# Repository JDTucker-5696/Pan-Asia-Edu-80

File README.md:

# Pan-Asia-Edu-80
Information about the Pan-Asia Edu-80 Z80 training system.

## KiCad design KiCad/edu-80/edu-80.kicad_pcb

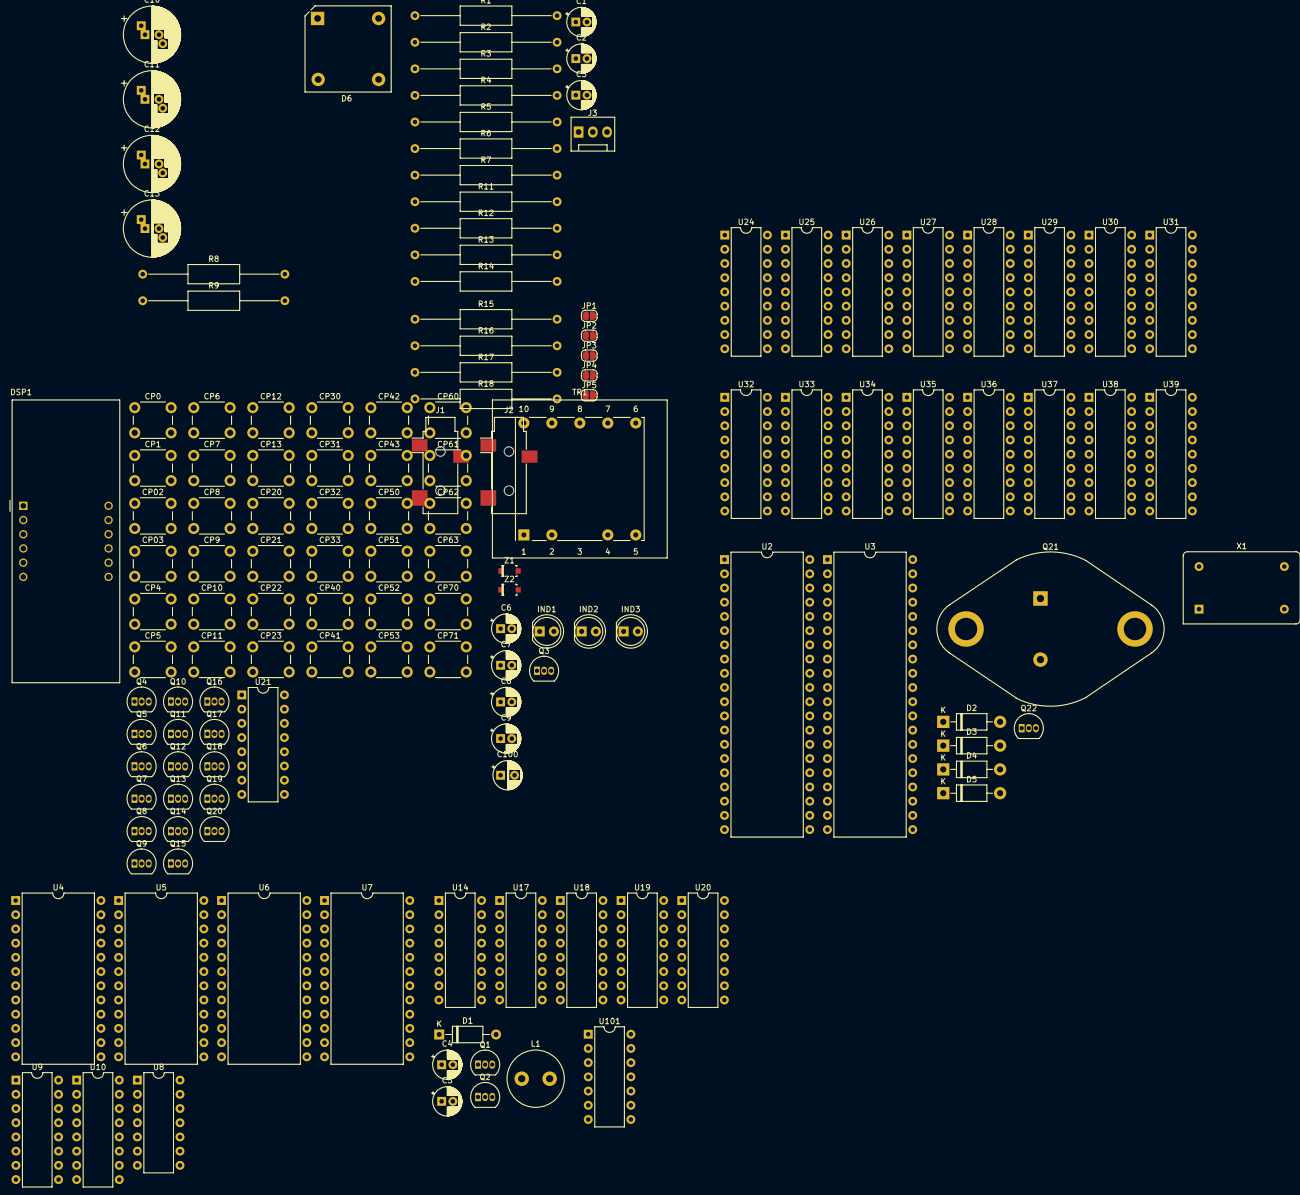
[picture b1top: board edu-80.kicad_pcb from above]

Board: 2 copper layers, 144 parts (0 on the bottom side), 110 nets, no tracks yet.

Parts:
C1: 20p; CP_Radial_D5.0mm_P2.00mm
C2: 10p; CP_Radial_D5.0mm_P2.00mm
C3: 250p; CP_Radial_D5.0mm_P2.00mm
C4, C5: 1uF; CP_Radial_D5.0mm_P2.00mm
C6, C7, C8, C9: 0.01uF; CP_Radial_D5.0mm_P2.00mm
C10, C13: 1000 uF (16v); CP_Radial_D10.0mm_P2.50mm_P5.00mm
C11: 100 uF (16v); CP_Radial_D10.0mm_P2.50mm_P5.00mm
C12: 2200 uF (16v); CP_Radial_D10.0mm_P2.50mm_P5.00mm
C100: 0.01uF; CP_Radial_D5.0mm_P2.50mm
CP0: 0; SW_PUSH_6mm
CP1: 1; SW_PUSH_6mm
CP02: 2; SW_PUSH_6mm
CP03: 3; SW_PUSH_6mm
CP4: RS; SW_PUSH_6mm
CP5: CK; SW_PUSH_6mm
CP6: K1; SW_PUSH_6mm
CP7: K2; SW_PUSH_6mm
CP8: K3; SW_PUSH_6mm
CP9: K4; SW_PUSH_6mm
CP10: 4; SW_PUSH_6mm
CP11: 5; SW_PUSH_6mm
CP12: 6; SW_PUSH_6mm
CP13: 7; SW_PUSH_6mm
CP20: 8; SW_PUSH_6mm
CP21: 9; SW_PUSH_6mm
CP22: A; SW_PUSH_6mm
CP23: B; SW_PUSH_6mm
CP30: C; SW_PUSH_6mm
CP31: D; SW_PUSH_6mm
CP32: E; SW_PUSH_6mm
CP33: F; SW_PUSH_6mm
CP40: GO; SW_PUSH_6mm
CP41: BR; SW_PUSH_6mm
CP42: PC; SW_PUSH_6mm
CP43: RG; SW_PUSH_6mm
CP50: MV; SW_PUSH_6mm
CP51: BN; SW_PUSH_6mm
CP52: TD; SW_PUSH_6mm
CP53: TL; SW_PUSH_6mm
CP60: RL; SW_PUSH_6mm
CP61: WI; SW_PUSH_6mm
CP62: AD; SW_PUSH_6mm
CP63: BI; SW_PUSH_6mm
CP70: +; SW_PUSH_6mm
CP71: -; SW_PUSH_6mm
D1: 1N914; D_A-405_P10.16mm_Horizontal
D2, D3, D4, D5: 1N4005; D_DO-41_SOD81_P10.16mm_Horizontal
D6: D_Bridge_+-AA; Diode_Bridge_15.1x15.1x6.3mm_P10.9mm
DSP1: Edu-80_Display; CA56-12EWA
IND1: HALT; LED_D5.0mm
IND2: WAIT; LED_D5.0mm
IND3: M1; LED_D5.0mm
J1: Audio Out; Jack_3.5mm_CUI_SJ-3523-SMT_Horizontal
J2: Audio In; Jack_3.5mm_CUI_SJ-3523-SMT_Horizontal
J3: Conn_01x03; FanPinHeader_1x03_P2.54mm_Vertical
JP1, JP2, JP3, JP4, JP5: SolderJumper_2_Open; SolderJumper-2_P1.3mm_Open_RoundedPad1.0x1.5mm
L1: 2MHz; L_Radial_D10.0mm_P5.00mm_Fastron_07M
Q1, Q2, Q3: ED1402; TO-92_Inline
Q4, Q5, Q6, Q7, Q8, Q9, Q10, Q11, Q12, Q13, Q14, Q15, Q16, Q17, Q18, Q19, Q20: ED1602; TO-92_Inline
Q21: 2N3055; TO-3
Q22: 2N3906; TO-92_Inline
R1, R15: 330; R_Axial_DIN0309_L9.0mm_D3.2mm_P25.40mm_Horizontal
R2, R11, R12, R13, R14: 4.7K; R_Axial_DIN0309_L9.0mm_D3.2mm_P25.40mm_Horizontal
R3: 1M; R_Axial_DIN0309_L9.0mm_D3.2mm_P25.40mm_Horizontal
R4, R5, R16, R17: 10K; R_Axial_DIN0309_L9.0mm_D3.2mm_P25.40mm_Horizontal
R6: 30K; R_Axial_DIN0309_L9.0mm_D3.2mm_P25.40mm_Horizontal
R7: 100K; R_Axial_DIN0309_L9.0mm_D3.2mm_P25.40mm_Horizontal
R8, R9: 470; R_Axial_DIN0309_L9.0mm_D3.2mm_P25.40mm_Horizontal
R18: 1K; R_Axial_DIN0309_L9.0mm_D3.2mm_P25.40mm_Horizontal
TR1: TRANSF7; Transformer_Breve_TEZ-28x33
U2: Z84C20; DIP-40_W15.24mm
U3: Z8430_CTC; DIP-40_W15.24mm
U4, U7: EPROM-2708; DIP-24_W15.24mm
U5: 2708_(2716); DIP-24_W15.24mm
U6: 6116_RAM; DIP-24_W15.24mm
U8: SN7432; DIP-14_W7.62mm
U9, U10, U21: 7442; DIP-16_W7.62mm
U14: PAL-002; DIP-16_W7.62mm
U17: PAL-001; DIP-16_W7.62mm
U18: CD4051; DIP-16_W7.62mm
U19, U20: CD4099; DIP-16_W7.62mm
U24, U25, U26, U27, U28, U29, U30, U31, U32, U33, U34, U35, U36, U37, U38, U39: 2111A; DIP-18_W7.62mm
U101: 7408; DIP-14_W7.62mm
X1: 20MHz Ocillator; Oscillator_DIP-14
Z1: 12.6v; SOD-123
Z2: 5.6v; SOD-123

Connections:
+5V: C11.1, C100.1, D1.1 (K), Q4.1 (E), Q5.1 (E), Q6.1 (E), Q7.1 (E), Q8.1 (E), Q9.1 (E), Q10.1 (E), Q11.1 (E), R1.1, R2.1, R4.1, R5.1, R7.2, R11.1, R12.1, R13.1, R14.1, R18.1, U2.26 (VCC), U3.24 (VCC), U4.18 (~PGM), U4.24 (VCC), U5.18 (~PGM_(~CE)), U5.24 (VCC), U6.24 (VCC), U7.18 (~PGM), U7.24 (VCC), U9.16 (VCC), U10.16 (VCC), U14.16 (VCC), U17.16 (VCC), U18.16 (VCC), U19.16 (VDD), U20.16 (VDD), U21.16 (VCC), U24.18 (VCC), U25.18 (VCC), U26.18 (VCC), U27.18 (VCC), U28.18 (VCC), U29.18 (VCC), U30.18 (VCC), U31.18 (VCC), U32.18 (VCC), U33.18 (VCC), U34.18 (VCC), U35.18 (VCC), U36.18 (VCC), U37.18 (VCC), U38.18 (VCC), U39.18 (VCC), U101.14 (VCC), X1.14 (Vcc)
+12V: JP1.1 (A), JP1.2 (B), JP4.1 (A), JP4.2 (B), Q21.2 (E), U4.19 (+12), U7.19 (+12)
-5V: JP2.1 (A), JP2.2 (B), JP3.1 (A), JP5.1 (A), JP5.2 (B), Q22.1 (E), U4.21 (-5V), U7.21 (-5V)
-ATI: C100.2, U18.1 (Y4)
A0: U2.6 (B/~A), U3.18 (CS0), U4.8 (A0), U5.8 (A0), U6.8 (A0), U7.8 (A0), U18.11 (S1), U19.5 (A0), U20.5 (A0), U24.17 (A4), U25.17 (A4), U26.17 (A4), U27.17 (A4), U28.17 (A4), U29.17 (A4), U30.17 (A4), U31.17 (A4), U32.17 (A4), U33.17 (A4), U34.17 (A4), U35.17 (A4), U36.17 (A4), U37.17 (A4), U38.17 (A4), U39.17 (A4)
A1: U2.5 (C/~D), U3.19 (CS1), U4.7 (A1), U5.7 (A1), U6.7 (A1), U7.7 (A1), U18.10 (S2), U19.6 (A1), U20.6 (A1), U24.7 (A7), U25.7 (A7), U26.7 (A7), U27.7 (A7), U28.7 (A7), U29.7 (A7), U30.7 (A7), U31.7 (A7), U32.7 (A7), U33.7 (A7), U34.7 (A7), U35.7 (A7), U36.7 (A7), U37.7 (A7), U38.7 (A7), U39.7 (A7)
A2: U4.6 (A2), U5.6 (A2), U6.6 (A2), U7.6 (A2), U18.9 (S3), U19.7 (A2), U20.7 (A2), U24.6 (A6), U25.6 (A6), U26.6 (A6), U27.6 (A6), U28.6 (A6), U29.6 (A6), U30.6 (A6), U31.6 (A6), U32.6 (A6), U33.6 (A6), U34.6 (A6), U35.6 (A6), U36.6 (A6), U37.6 (A6), U38.6 (A6), U39.6 (A6)
A3: U4.5 (A3), U5.5 (A3), U6.5 (A3), U7.5 (A3), U14.11 (D), U24.5 (A5), U25.5 (A5), U26.5 (A5), U27.5 (A5), U28.5 (A5), U29.5 (A5), U30.5 (A5), U31.5 (A5), U32.5 (A5), U33.5 (A5), U34.5 (A5), U35.5 (A5), U36.5 (A5), U37.5 (A5), U38.5 (A5), U39.5 (A5)
A4: U4.4 (A4), U5.4 (A4), U6.4 (A4), U7.4 (A4), U14.12 (C), U24.4 (A0), U25.4 (A0), U26.4 (A0), U27.4 (A0), U28.4 (A0), U29.4 (A0), U30.4 (A0), U31.4 (A0), U32.4 (A0), U33.4 (A0), U34.4 (A0), U35.4 (A0), U36.4 (A0), U37.4 (A0), U38.4 (A0), U39.4 (A0)
A5: U4.3 (A5), U5.3 (A5), U6.3 (A5), U7.3 (A5), U14.13 (B), U24.3 (A1), U25.3 (A1), U26.3 (A1), U27.3 (A1), U28.3 (A1), U29.3 (A1), U30.3 (A1), U31.3 (A1), U32.3 (A1), U33.3 (A1), U34.3 (A1), U35.3 (A1), U36.3 (A1), U37.3 (A1), U38.3 (A1), U39.3 (A1)
A6: U4.2 (A6), U5.2 (A6), U6.2 (A6), U7.2 (A6), U14.10 (A), U24.2 (A2), U25.2 (A2), U26.2 (A2), U27.2 (A2), U28.2 (A2), U29.2 (A2), U30.2 (A2), U31.2 (A2), U32.2 (A2), U33.2 (A2), U34.2 (A2), U35.2 (A2), U36.2 (A2), U37.2 (A2), U38.2 (A2), U39.2 (A2)
A7: U4.1 (A7), U5.1 (A7), U6.1 (A7), U7.1 (A7), U17.10 (A), U24.1 (A3), U25.1 (A3), U26.1 (A3), U27.1 (A3), U28.1 (A3), U29.1 (A3), U30.1 (A3), U31.1 (A3), U32.1 (A3), U33.1 (A3), U34.1 (A3), U35.1 (A3), U36.1 (A3), U37.1 (A3), U38.1 (A3), U39.1 (A3)
A8: U4.23 (A8), U5.23 (A8), U6.23 (A8), U7.23 (A8), U10.15 (A0)
A9: U4.22 (A9), U5.22 (A9), U6.22 (A9), U7.22 (A9), U10.14 (A1)
A10: U5.19 (+12_(A10)), U6.19 (A10), U9.15 (A0), U10.13 (A2)
CKCTL: R4.2, U20.1 (Q7)
CKKEY: CP5.1 (X1), R5.2, R6.2
CLK: Q1.3 (C), R1.2, U2.25 (CLK), U3.15 (CLK)
CM1: U9.5 (~Q4), U24.15 (~CE2), U25.15 (~CE2), U26.15 (~CE2), U27.15 (~CE2), U28.15 (~CE2), U29.15 (~CE2), U30.15 (~CE2), U31.15 (~CE2)
CM2: U9.6 (~Q5), U32.15 (~CE2), U33.15 (~CE2), U34.15 (~CE2), U35.15 (~CE2), U36.15 (~CE2), U37.15 (~CE2), U38.15 (~CE2), U39.15 (~CE2)
D0: U2.19 (D0), U3.25 (D0), U4.9 (D0), U5.9 (D0), U6.9 (D0), U7.9 (D0), U19.3 (Din), U20.3 (Din), U24.13 (D3), U26.13 (D3), U28.13 (D3), U30.13 (D3), U32.13 (D3), U34.13 (D3), U36.13 (D3), U38.13 (D3)
D1: U2.20 (D1), U4.10 (D1), U5.10 (D1), U6.10 (D1), U7.10 (D1), U24.12 (D2), U26.12 (D2), U28.12 (D2), U30.12 (D2), U32.12 (D2), U34.12 (D2), U36.12 (D2), U38.12 (D2)
D2: U2.1 (D2), U3.27 (D2), U4.11 (D2), U5.11 (D2), U6.11 (D2), U7.11 (D2), U24.11 (D1), U26.11 (D1), U28.11 (D1), U30.11 (D1), U32.11 (D1), U34.11 (D1), U36.11 (D1), U38.11 (D1)
D3: U2.40 (D3), U3.28 (D3), U4.13 (D3), U5.13 (D3), U6.13 (D3), U7.13 (D3), U24.14 (D4), U26.14 (D4), U28.14 (D4), U30.14 (D4), U32.14 (D4), U34.14 (D4), U36.14 (D4), U38.14 (D4)
D4: U2.39 (D4), U3.1 (D4), U4.14 (D4), U5.14 (D4), U6.14 (D4), U7.14 (D4), U25.14 (D4), U27.14 (D4), U29.14 (D4), U31.14 (D4), U33.14 (D4), U35.14 (D4), U37.14 (D4), U39.14 (D4)
D5: U2.38 (D5), U3.2 (D5), U4.15 (D5), U5.15 (D5), U6.15 (D5), U7.15 (D5), U25.13 (D3), U27.13 (D3), U29.13 (D3), U31.13 (D3), U33.13 (D3), U35.13 (D3), U37.13 (D3), U39.13 (D3)
D6: U2.3 (D6), U3.3 (D6), U4.16 (D6), U5.16 (D6), U6.16 (D6), U7.16 (D6), U25.12 (D2), U27.12 (D2), U29.12 (D2), U31.12 (D2), U33.12 (D2), U35.12 (D2), U37.12 (D2), U39.12 (D2)
D7: U2.2 (D7), U3.4 (D7), U4.17 (D7), U5.17 (D7), U6.17 (D7), U7.17 (D7), U18.3 (Z), U25.11 (D1), U27.11 (D1), U29.11 (D1), U31.11 (D1), U33.11 (D1), U35.11 (D1), U37.11 (D1), U39.11 (D1)
DSPOUT0: Q4.2 (B), U19.9 (Q0)
DSPOUT1: Q5.2 (B), U19.10 (Q1)
DSPOUT2: Q6.2 (B), U19.11 (Q2)
DSPOUT3: Q7.2 (B), U19.12 (Q3)
DSPOUT4: Q8.2 (B), U19.13 (Q4)
DSPOUT5: Q9.2 (B), U19.14 (Q5)
DSPOUT6: Q10.2 (B), U19.15 (Q6)
DSPOUT7: Q11.2 (B), U19.1 (Q7)
Earth: C2.2, C4.2, C5.2, C7.2, C10.2, C11.2, C12.2, C13.1, CP4.2 (Y1), CP5.2 (Y1), CP6.2 (Y1), CP7.2 (Y1), CP8.2 (Y1), CP9.2 (Y1), D6.2 (-), IND1.1 (K), IND2.1 (K), IND3.1 (K), Q1.1 (E), Q2.1 (E), Q3.1 (E), R15.2, TR1.9, U2.11 (GND), U4.12 (GND), U5.12 (GND), U6.12 (GND), U7.12 (GND), U9.8 (GND), U10.8 (GND), U10.12 (A3), U14.8 (GND), U17.8 (GND), U18.7 (VEE), U18.8 (GND), U19.2 (CLR), U19.8 (VSS), U20.2 (CLR), U20.8 (VSS), U21.8 (GND), U24.8 (GND), U25.8 (GND), U26.8 (GND), U27.8 (GND), U28.8 (GND), U29.8 (GND), U30.8 (GND), U31.8 (GND), U32.8 (GND), U33.8 (GND), U34.8 (GND), U35.8 (GND), U36.8 (GND), U37.8 (GND), U38.8 (GND), U39.8 (GND), X1.7 (GND), Z1.A, Z2.K
KEYDSP0: U20.9 (Q0), U21.15 (A0)
KEYDSP1: U20.10 (Q1), U21.14 (A1)
KEYDSP2: U20.11 (Q2), U21.13 (A2)
KEYDSP3: U20.12 (Q3), U21.12 (A3)
KEYIN0: CP0.1 (X1), CP10.1 (X1), CP20.1 (X1), CP30.2 (Y1), CP40.1 (X1), CP50.1 (X1), CP60.1 (X1), CP70.1 (X1), U18.13 (Y0)
KEYIN1: CP1.1 (X1), CP11.1 (X1), CP21.1 (X1), CP31.1 (X1), CP41.1 (X1), CP51.1 (X1), CP61.1 (X1), CP71.1 (X1), U18.14 (Y1)
KEYIN2: CP02.1 (X1), CP12.1 (X1), CP22.1 (X1), CP32.1 (X1), CP42.1 (X1), CP52.1 (X1), CP62.1 (X1), U18.15 (Y2)
KEYIN3: CP03.1 (X1), CP13.1 (X1), CP23.1 (X1), CP33.1 (X1), CP43.1 (X1), CP53.1 (X1), CP63.1 (X1), U18.12 (Y3)
MP: U8.12, U20.15 (Q6)
MRP: U8.11, U24.16 (R/W), U25.16 (R/W), U26.16 (R/W), U27.16 (R/W), U28.16 (R/W), U29.16 (R/W), U30.16 (R/W), U31.16 (R/W)
unnamed: C1.1, L1.1
unnamed: C3.1, R2.2
unnamed: C4.1, R6.1
unnamed: C6.2, C7.1
unnamed: C8.1, R16.1
unnamed: C9.2, R17.1, R18.2
unnamed: CP0.2 (Y1), CP1.2 (Y1), CP02.2 (Y1), CP03.2 (Y1), Q12.2 (B), U21.1 (~Q0)
unnamed: CP10.2 (Y1), CP11.2 (Y1), CP12.2 (Y1), CP13.2 (Y1), Q13.2 (B), U21.2 (~Q1)
unnamed: CP20.2 (Y1), CP21.2 (Y1), CP22.2 (Y1), CP23.2 (Y1), Q14.2 (B), U21.3 (~Q2)
unnamed: CP30.1 (X1), CP31.2 (Y1), CP32.2 (Y1), CP33.2 (Y1), Q15.2 (B), U21.4 (~Q3)
unnamed: CP40.2 (Y1), CP41.2 (Y1), CP42.2 (Y1), CP43.2 (Y1), Q16.2 (B), U21.5 (~Q4)
unnamed: CP50.2 (Y1), CP51.2 (Y1), CP52.2 (Y1), CP53.2 (Y1), Q17.2 (B), U21.6 (~Q5)
unnamed: CP60.2 (Y1), CP61.2 (Y1), CP62.2 (Y1), CP63.2 (Y1), Q18.2 (B), U21.7 (~Q6)
unnamed: CP70.2 (Y1), CP71.2 (Y1), Q19.2 (B), U21.9 (~Q7)
unnamed: D2.2 (A), D4.1 (K), TR1.8, TR1.10
unnamed: C12.1, D2.1 (K), D3.1 (K)
unnamed: D3.2 (A), D5.1 (K)
unnamed: C13.2, D4.2 (A), D5.2 (A), Q22.3 (C), R8.2
unnamed: C10.1, D6.1 (+), Q21.3 (C), R9.2
unnamed: D6.3, TR1.7
unnamed: D6.4, TR1.5
unnamed: DSP1.12 (CA4), Q15.3 (C)
unnamed: DSP1.10 (CA5), Q16.3 (C)
unnamed: DSP1.8 (CA6), Q17.3 (C)
unnamed: DSP1.6 (CA7), Q18.3 (C)
unnamed: DSP1.4 (CA8), Q19.3 (C)
unnamed: DSP1.2 (CA9), Q20.3 (C)
unnamed: DSP1.9 (DPX), Q11.3 (C)
unnamed: DSP1.3 (a), Q4.3 (C)
unnamed: DSP1.5 (b), Q5.3 (C)
unnamed: DSP1.7 (c), Q6.3 (C)
unnamed: DSP1.11 (d), Q7.3 (C)
unnamed: IND3.2 (A), Q3.3 (C)
unnamed: C1.2, C2.1, J3.3, R3.2
unnamed: JP3.2 (B), U5.21 (-5V_(VPP))
unnamed: L1.2, R3.1
unnamed: Q12.3 (C), Q13.1 (E), Q14.1 (E), Q15.1 (E), Q16.1 (E), Q17.1 (E), Q18.1 (E), Q19.1 (E), Q20.1 (E)
unnamed: Q20.2 (B), U21.10 (~Q8)
unnamed: Q21.1 (B), R9.1, Z1.K
unnamed: Q22.2 (B), R8.1, Z2.A
unnamed: TR1.2, TR1.4
unnamed: U8.6, U8.9
unnamed: U8.3, U8.10
unnamed: U8.8, U9.12 (A3)
unnamed: C9.1, R16.2, R17.2
~CE-U4: U4.20 (~CE), U9.1 (~Q0), U101.2
~CE-U5: U5.20 (~CS_(~OE)), U9.2 (~Q1), U101.1
~CE-U6: U6.18 (~CE), U6.20 (~OE), U9.3 (~Q2), U101.13
~CE-U7: U7.20 (~CE), U9.4 (~Q3), U101.12
~IORQ: U2.36 (~IORQ), U3.10 (~IORQ), U17.11 (D)
~IRQ: Q2.3 (C), R11.2, U2.23 (~INT), U3.12 (~INT)
~M1: U2.37 (~M1), U3.14 (~M1)
~ME1: U10.1 (~Q0), U24.10 (~CE1), U25.10 (~CE1)
~ME2: U10.2 (~Q1), U26.10 (~CE1), U27.10 (~CE1)
~ME3: U10.3 (~Q2), U28.10 (~CE1), U29.10 (~CE1)
~ME4: U10.4 (~Q3), U30.10 (~CE1), U31.10 (~CE1)
~ME5: U10.5 (~Q4), U32.10 (~CE1), U33.10 (~CE1)
~ME6: U10.6 (~Q5), U34.10 (~CE1), U35.10 (~CE1)
~ME7: U10.7 (~Q6), U36.10 (~CE1), U37.10 (~CE1)
~ME8: U10.9 (~Q7), U38.10 (~CE1), U39.10 (~CE1)
~RD: U2.35 (~RD), U3.6 (~RD), U17.12 (C), U24.9 (~OE), U25.9 (~OE), U26.9 (~OE), U27.9 (~OE), U28.9 (~OE), U29.9 (~OE), U30.9 (~OE), U31.9 (~OE), U32.9 (~OE), U33.9 (~OE), U34.9 (~OE), U35.9 (~OE), U36.9 (~OE), U37.9 (~OE), U38.9 (~OE), U39.9 (~OE)
~RST: C5.1, CP4.1 (X1), D1.2 (A), R7.1, U3.17 (~RESET)
~WR: U6.21 (~WE), U8.13, U17.13 (B), U32.16 (R/W), U33.16 (R/W), U34.16 (R/W), U35.16 (R/W), U36.16 (R/W), U37.16 (R/W), U38.16 (R/W), U39.16 (R/W)

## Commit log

2023-05-19 Add files via upload
    EPROM HEX and BIN files: original EPROM, EPROM with loader/2716 programmer @ 0x0400, EPROM without loader, EPROM with reconstructed code.
2023-05-19 Renamed dir Edu-80 to EPROMs.
2023-05-19 Fixing file extentions in EPROMs.
2023-05-19 Add files via upload
    Learning about moving files around in GIT, and fixing file extensions in EPROMs.
2023-05-23 Trying to include the KiCad project for the schematics. Includes submodules lib/digikey-kicad-library, sym/Z80-CPU-for-KICAD, and sym/kicad-symbols
2023-06-02 cleaning up KiCad project
2023-06-03 Fixed lst of the errors, still two warnings
2023-06-03 Working on removing edu-80-rescue symbol library
2023-06-04 Cleaning up the PAL-003 decoding, adding Modifications page.
2023-06-06 Fixed ~IRQ vs. INT for PIO/CTC. Removed old (version 5) schematic files.
2023-06-06 removing more old files.
2023-06-10 Removing more useless (old) files.
2023-06-10 Deleting more old files.
2023-08-12 Fixed the last of the EDR warnings/errors, adding footprints
2023-09-22 Adding footprints.
